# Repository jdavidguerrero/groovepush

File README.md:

# GroovePush

**DIY Ableton Push 3 clone + AI mix-copilot surface for the GroovePilot platform.**

A monorepo unifying the three layers of the controller:

| Layer | Path | Stack | Target |
|---|---|---|---|
| **Processor / firmware** | [`apps/processor`](apps/processor) | C++ / Arduino (PlatformIO) | Teensy 4.1 (brain) + NeoTrellis M4 (8×4 pads) |
| **GUI** | [`apps/gui`](apps/gui) | C++ / Qt 6 / QML | Raspberry Pi 5 + 5" DSI display |
| **Hardware** | [`hardware/`](hardware) | KiCad | Main PCB / interconnect |

Planning & contracts live in [`specs/`](specs) and [`docs/`](docs).

---

## Architecture at a glance

```
     ┌───────────────┐   USB-MIDI (class-compliant, <5ms)   ┌──────────┐
     │  Teensy 4.1   │─────────────────────────────────────▶│  Ableton │
     │  (Processor)  │                                       │   Live   │
     │  pads·enc·    │◀───── SysEx / Remote Script ──────────│          │
     │  faders·piezo │                                       └──────────┘
     └──────┬────────┘
            │ UART 1 Mbps (binary framing / SysEx)
            │  + I2C to 2× NeoTrellis (pads/LEDs)
     ┌──────┴────────┐   Serial (QSerialPort)   ┌───────────────────────┐
     │ NeoTrellis M4 │                          │  Raspberry Pi 5 (GUI) │
     │  8×4 pad grid │◀────── UART link ───────▶│  Qt/QML 5" display     │
     └───────────────┘                          │  + cloud AI (GroovePilot)
                                                 └───────────────────────┘
```

- **Performance MIDI never touches the network** — pads/encoders/faders reach Live as USB-MIDI from the Teensy.
- **The RPi5 GUI** is a thin, low-latency remote + the AI mix copilot surface.
- Wire protocol between Teensy ↔ M4 ↔ RPi is documented in [`specs/`](specs) and `apps/processor/include/shared/`.

## Repo layout

```
GroovePush/
├── apps/
│   ├── gui/          # Qt6/QML GUI (Raspberry Pi 5) — imported with full git history
│   └── processor/    # PlatformIO firmware (Teensy 4.1 + NeoTrellis M4) — full git history
├── hardware/         # KiCad project (schematic + PCB)
├── specs/            # OpenSpec-style specifications (source of truth for implementation)
├── docs/             # Design specs, guides, ADRs
├── .claude/          # Shared AI context, agents, and SDD harness
├── Makefile          # No-Node fallback orchestration
├── package.json      # pnpm workspace orchestration
└── pnpm-workspace.yaml
```

## Getting started

```bash
# With pnpm (workspace orchestration)
pnpm install
pnpm processor:build      # build firmware (PlatformIO)
pnpm gui:build            # build the Qt GUI

# Or with make (no Node required)
make help
make proc-build-teensy
make gui-build
```

### Prerequisites
- **Processor**: [PlatformIO Core](https://platformio.org/) (`pip install platformio`)
- **GUI**: Qt 6.8+, CMake ≥ 3.16 (see [`apps/gui/README_SETUP.md`](apps/gui/README_SETUP.md))
- **Hardware**: KiCad 8+

## History

`apps/gui` and `apps/processor` were previously two standalone GitHub repos
(`ableton_push_clone_gui`, `ableton_push_clone_processor`). They were merged into
this monorepo **preserving their full commit history** via `git subtree` merge.
The original remotes are preserved in `docs/MONOREPO_MIGRATION.md`.

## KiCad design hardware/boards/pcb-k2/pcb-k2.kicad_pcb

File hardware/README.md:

# GroovePush — Hardware (KiCad)

Modular hierarchical schematic for the GroovePush controller. See
[ADR-0001](../specs/adr/0001-modular-pcb-topology.md) for the topology decision.

- **Project**: `GroovePush.kicad_pro`
- **KiCad**: v10 (files `version 20260101`)
- **Root sheet**: `GroovePush.kicad_sch` → 4 sub-sheets (one per module / future PCB):
  `processor.kicad_sch`, `encoders.kicad_sch`, `analog.kicad_sch`, `leds.kicad_sch`.

## System topology

```
        ┌────────────────── PROCESSOR BOARD ──────────────────┐
        │  Teensy 4.1 (J1 socket)                              │
 +5V ──▶│  ├─ I2C ─ 2× MCP23017 (U1 0x20 sw, U2 0x21 btn)      │
 PSU  J4│  ├─ 4.7k I2C pull-ups (R1,R2)                        │
        │  └─ decoupling C1/C2/C3                              │
        │   J2      J3       J5/J8      J6        J7      J20   │
        └───┼───────┼─────────┼─────────┼─────────┼───────┼────┘
        I2C │  UART │  ribbon │ ribbon  │  3-wire │ ribbon│
        ┌───▼──┐ ┌──▼───┐ ┌───▼────┐ ┌──▼─────┐ ┌─▼────┐ │ panel
        │Neo-  │ │ RPi5 │ │ENCODER │ │ ANALOG │ │ LED  │ │ buttons
        │Trellis│ │ GUI │ │ board  │ │ board  │ │board │
        └──────┘ └──────┘ └────────┘ └────────┘ └──────┘
```

Each sub-sheet is electrically self-contained and exposes a header — it can become its
own PCB. The inter-board wiring is the **connector contract** in the table below.

## Bill of Materials (initial)

### Processor board (`processor.kicad_sch`)
| Ref | Value | Part | Notes |
|-----|-------|------|-------|
| J1 | Teensy 4.1 socket | 2×24 female header | The Teensy is a module; socket pinout must be mapped to the real Teensy 4.1 footprint before layout |
| U1 | MCP23017 @ 0x20 | I²C 16-bit I/O expander | 8 encoder push-switches (GPA0–6 + GPB0) |
| U2 | MCP23017 @ 0x21 | I²C 16-bit I/O expander | 8 extra panel buttons (GPA0–6 + GPB0) |
| R1, R2 | 4.7 kΩ | I²C pull-ups | SDA / SCL to +3V3 |
| C1, C2 | 100 nF | Decoupling | 1 per MCP23017 |
| C3 | 10 µF | Bulk | +5V rail |
| J2 | 1×4 | NeoTrellis I²C | SDA, SCL, +3V3, GND |
| J3 | 1×4 | RPi5 UART | TX, RX, GND, GND |
| J4 | 1×2 | 5 V power in | +5V, GND |
| J5 | 2×8 | Encoder A/B ribbon | 16 quadrature lines |
| J6 | 1×12 | Analog board | 4 fader + 4 piezo + 2 IR + 3V3 + GND |
| J7 | 1×3 | LED board | LED_DATA, +5V, GND |
| J8 | 1×10 | Encoder switches | 8 switches + GND |
| J20 | 1×10 | Panel buttons | 8 buttons + 2 GND |

### Encoder board (`encoders.kicad_sch`)
| Ref | Value | Part | Notes |
|-----|-------|------|-------|
| RE1–RE8 | EC11 | Rotary encoder + switch | A/B quadrature + push |
| J9 | 2×8 | A/B to processor | mates J5 |
| J10 | 1×10 | Switches to processor | mates J8 |

### Analog board (`analog.kicad_sch`)
| Ref | Value | Part | Notes |
|-----|-------|------|-------|
| RV1–RV4 | ALPS B50K | Slide potentiometer (fader) | wiper → ADC |
| J12–J15 | 1×2 | Piezo element | signal + GND |
| R3–R6 | 1 MΩ | Piezo bleed | across each piezo |
| J16, J17 | 1×3 | Sharp IR sensor | +3V3, GND, OUT |
| J11 | 1×12 | To processor | mates J6 |

### LED board (`leds.kicad_sch`)
| Ref | Value | Part | Notes |
|-----|-------|------|-------|
| U3 | SN74LVC245A | Level shifter 3.3→5 V | data line to strip |
| R7 | 330 Ω | Series | data protection |
| D1 | WS2812B | First pixel (strip = 28) | DIN←data, DOUT→strip |
| C4 | 1000 µF | Bulk | +5V near LEDs |
| C5 | 100 nF | Decoupling | U3 |
| J18 | 1×3 | To LED strip | +5V, DATA, GND |
| J19 | 1×3 | To processor | mates J7 |

## Inter-board connector contract

| Processor conn | Mates | Signals | Cable |
|---|---|---|---|
| J2 | NeoTrellis board | I2C_SDA, I2C_SCL, +3V3, GND | 4-wire |
| J3 | Raspberry Pi 5 | TEENSY_TX1→RPi_RX, TEENSY_RX1→RPi_TX, GND, GND | 4-wire (do **not** power the Pi from here) |
| J4 | 5 V PSU | +5V, GND | 5 V / 3 A min |
| J5 ↔ J9 | Encoder board | ENC1..8 A/B (16) | 16-way ribbon |
| J8 ↔ J10 | Encoder board | ENC_SW1..8, GND | 10-way ribbon |
| J6 ↔ J11 | Analog board | FADER1..4, PIEZO1..4, IR1..2, +3V3, GND | 12-way |
| J7 ↔ J19 | LED board | LED_DATA, +5V, GND | 3-wire |
| J20 | Panel buttons | BTN1..8, GND | 10-way |

## Power budget (from `apps/processor/PIN_DISTRIBUTION.md`)
| Rail | Load | Current |
|---|---|---|
| +5V | NeoPixels (28 @ full) | ~1.7 A |
| +5V | Teensy 4.1 | ~0.15 A |
| +3V3 | 2× NeoTrellis, MCP, encoders, sensors | ~0.25 A |
| **Total** | | **5 V / 3 A PSU minimum** |

## Verification status
Connectivity validated via the KiCad MCP net lister (all nets ≥ 2 pins; power rails carry
`PWR_FLAG`; unused MCP/level-shifter pins marked no-connect). Full ERC/netlist export via
`kicad-cli` was **not run in this environment** (no `kicad-cli` on PATH). Open the project
in KiCad 10 and run ERC before layout.

## Known issues / next steps (see `../GAPS_AND_IMPROVEMENTS.md`)
1. **Footprints not yet assigned** — this is schematic-only. Assign before PCB layout.
2. **Teensy socket pin mapping** — J1 pins are logical; map to the real Teensy 4.1
   footprint (verify each GPIO ↔ socket position) before layout.
3. **I2C vs UART NeoTrellis** — this design uses I²C NeoTrellis (0x2E/0x2F) per the user's
   build; the firmware's `UART_CONNECTIONS.md` (NeoTrellis **M4** over UART) is an
   alternative. Reconcile firmware `Config.h` accordingly.
4. **Sharp IR level** — powered from +3V3; select a 3.3 V-compatible rangefinder, or add a
   divider if using a 5 V GP2Y0A part (its output can exceed 3.3 V).
5. **MCP23017 GPA7/GPB7** are output-only (erratum) — intentionally not used as inputs.
6. **Encoder A/B pull-ups** — rely on Teensy internal pull-ups; add external 10 k if noisy.

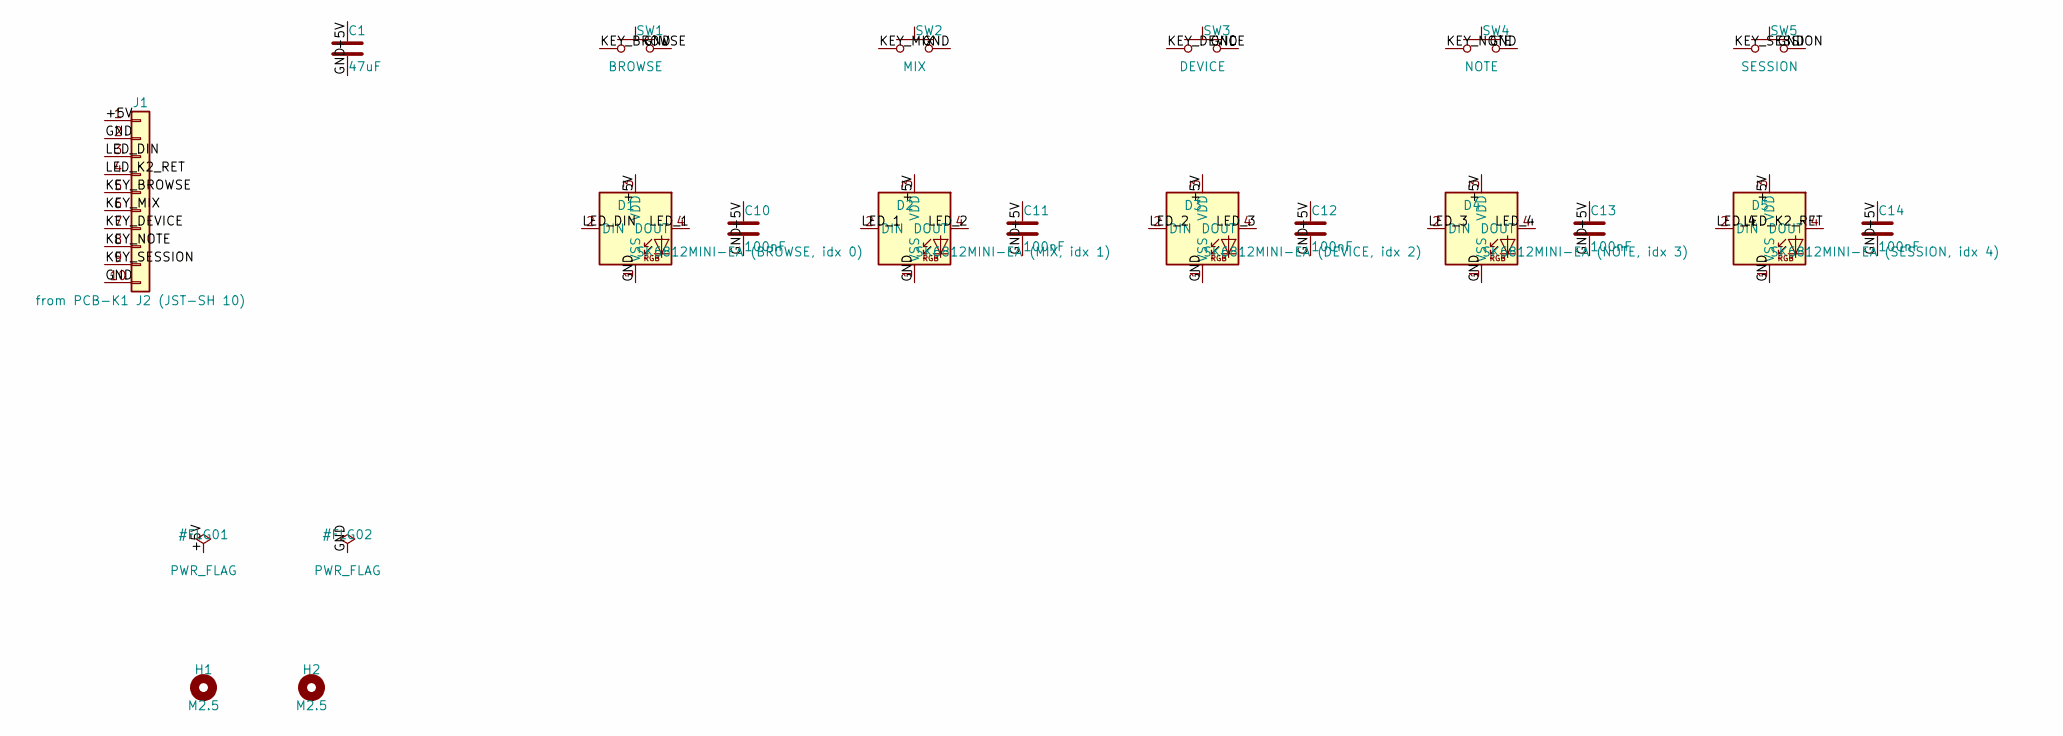
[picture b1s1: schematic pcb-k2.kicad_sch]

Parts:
C1: 47uF; C_1206_3216Metric
C10, C11, C12, C13, C14: 100nF; C_0603_1608Metric
D1: SK6812MINI-EA (BROWSE, idx 0); LED_SK6812MINI-E_3.2x2.8mm_P1.5mm_ReverseMount
D2: SK6812MINI-EA (MIX, idx 1); LED_SK6812MINI-E_3.2x2.8mm_P1.5mm_ReverseMount
D3: SK6812MINI-EA (DEVICE, idx 2); LED_SK6812MINI-E_3.2x2.8mm_P1.5mm_ReverseMount
D4: SK6812MINI-EA (NOTE, idx 3); LED_SK6812MINI-E_3.2x2.8mm_P1.5mm_ReverseMount
D5: SK6812MINI-EA (SESSION, idx 4); LED_SK6812MINI-E_3.2x2.8mm_P1.5mm_ReverseMount
H1, H2: M2.5; MountingHole_2.7mm_M2.5
J1: from PCB-K1 J2 (JST-SH 10); JST_SH_SM10B-SRSS-TB_1x10-1MP_P1.00mm_Horizontal
SW1: BROWSE; SW_Kailh_Choc_V2_1u
SW2: MIX; SW_Kailh_Choc_V2_1u
SW3: DEVICE; SW_Kailh_Choc_V2_1u
SW4: NOTE; SW_Kailh_Choc_V2_1u
SW5: SESSION; SW_Kailh_Choc_V2_1u

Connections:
/+5V: C1.1, C10.1, C11.1, C12.1, C13.1, C14.1, D1.3 (VDD), D2.3 (VDD), D3.3 (VDD), D4.3 (VDD), D5.3 (VDD), J1.1
/GND: C1.2, C10.2, C11.2, C12.2, C13.2, C14.2, D1.1 (VSS), D2.1 (VSS), D3.1 (VSS), D4.1 (VSS), D5.1 (VSS), J1.2, J1.10, SW1.2, SW2.2, SW3.2, SW4.2, SW5.2
/KEY_BROWSE: J1.5, SW1.1
/KEY_DEVICE: J1.7, SW3.1
/KEY_MIX: J1.6, SW2.1
/KEY_NOTE: J1.8, SW4.1
/KEY_SESSION: J1.9, SW5.1
/LED_1: D1.4 (DOUT), D2.2 (DIN)
/LED_2: D2.4 (DOUT), D3.2 (DIN)
/LED_3: D3.4 (DOUT), D4.2 (DIN)
/LED_4: D4.4 (DOUT), D5.2 (DIN)
/LED_DIN: D1.2 (DIN), J1.3
/LED_K2_RET: D5.4 (DOUT), J1.4

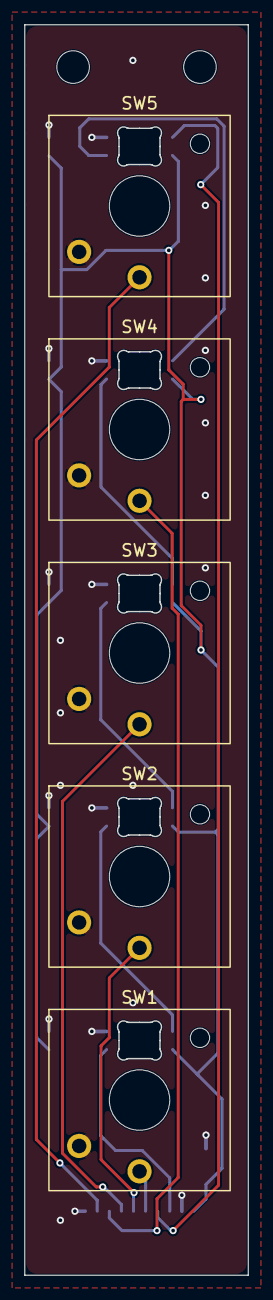
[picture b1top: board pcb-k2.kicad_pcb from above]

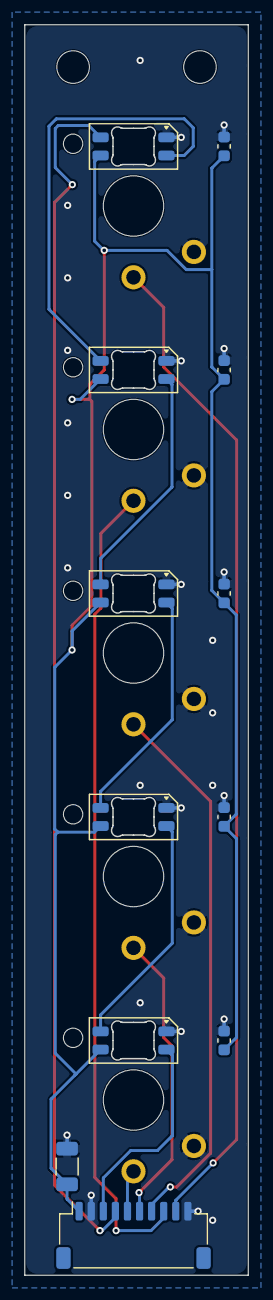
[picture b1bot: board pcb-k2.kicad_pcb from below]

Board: 2 copper layers, 18.5 x 103.5 mm, 19 parts (12 on the bottom side), 13 nets.

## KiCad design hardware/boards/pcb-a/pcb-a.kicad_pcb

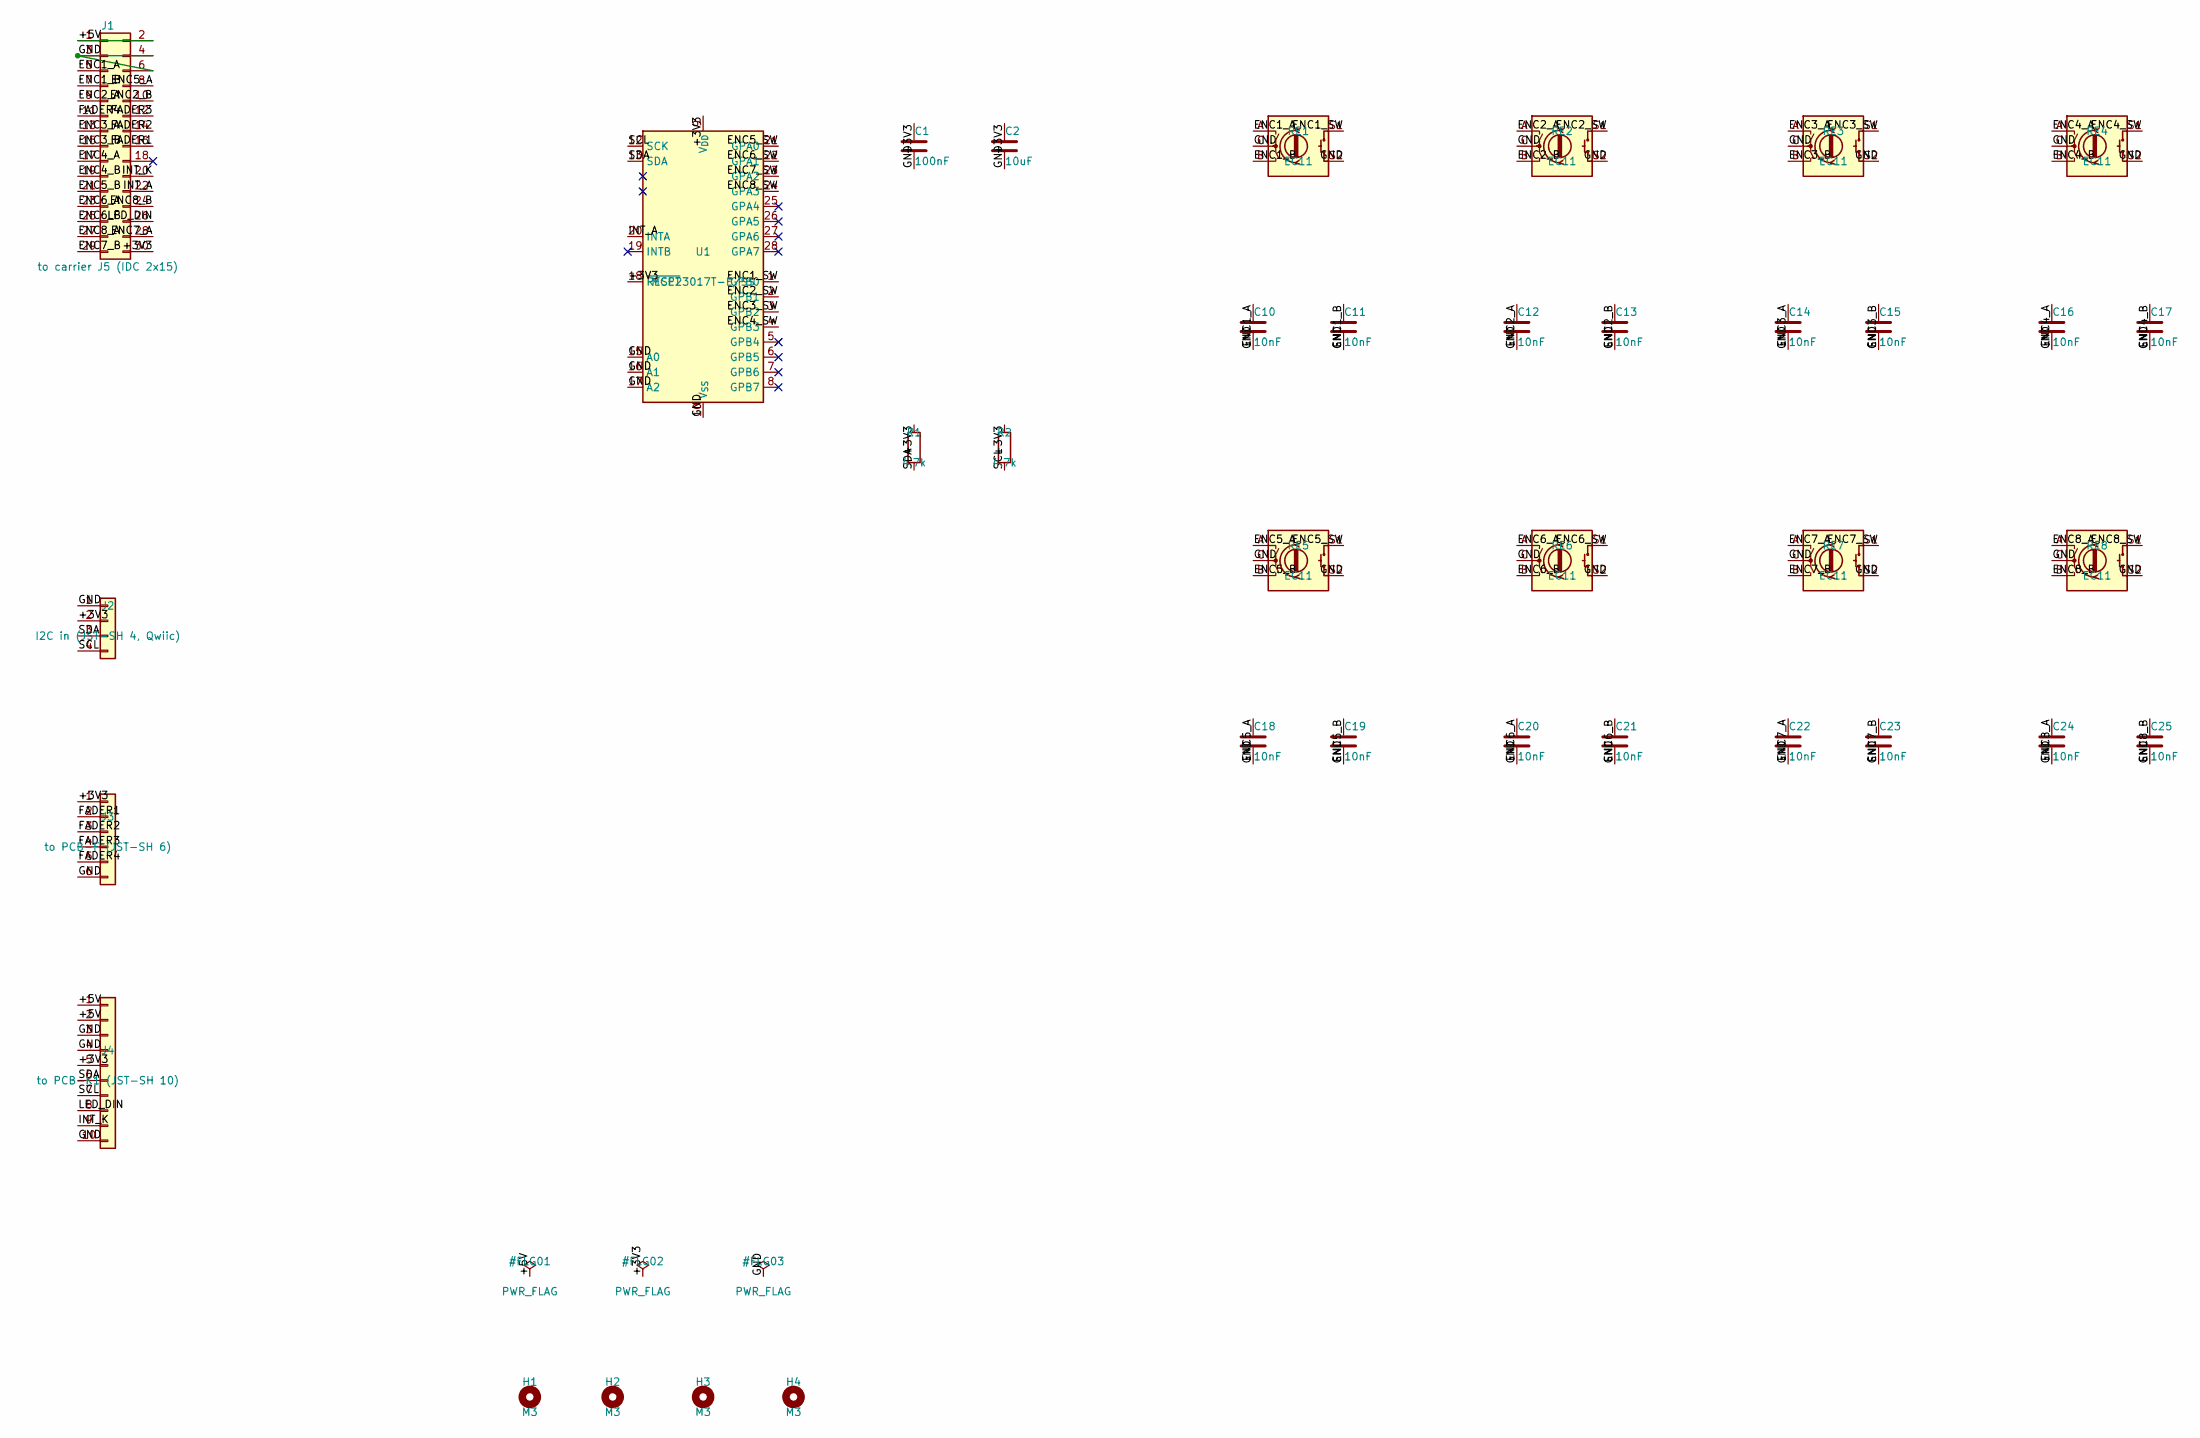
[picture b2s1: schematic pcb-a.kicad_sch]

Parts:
C1: 100nF; C_0603_1608Metric; LCSC C14663
C2: 10uF; C_0805_2012Metric; LCSC C15850
C10, C11, C12, C13, C14, C15, C16, C17, C18, C19, C20, C21, C22, C23, C24, C25: 10nF; C_0603_1608Metric; LCSC C57112
H1, H2, H3, H4: M3; MountingHole_3.2mm_M3
J1: to carrier J5 (IDC 2x15); IDC-Header_2x15_P2.54mm_Vertical
J2: I2C in (JST-SH 4, Qwiic); JST_SH_SM04B-SRSS-TB_1x04-1MP_P1.00mm_Horizontal; LCSC C160404
J3: to PCB-F (JST-SH 6); JST_SH_SM06B-SRSS-TB_1x06-1MP_P1.00mm_Horizontal; LCSC C160405
J4: to PCB-K1 (JST-SH 10); JST_SH_SM10B-SRSS-TB_1x10-1MP_P1.00mm_Horizontal; LCSC C160409
R1, R2: 4.7k; R_0603_1608Metric; LCSC C23162
RE1, RE2, RE3, RE4, RE5, RE6, RE7, RE8: EC11; RotaryEncoder_Alps_EC11E-Switch_Vertical_H20mm
U1: MCP23017T-E/SS; SSOP-28_5.3x10.2mm_P0.65mm; LCSC C558584

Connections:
/+3V3: C1.1, C2.1, J1.30, J2.2, J3.1, J4.5, R1.1, R2.1, U1.9 (V_{DD}), U1.18 (~RESET)
/+5V: J1.1, J1.2, J4.1, J4.2
/ENC1_A: C10.1, J1.5, RE1.A
/ENC1_B: C11.1, J1.7, RE1.B
/ENC1_SW: RE1.S1, U1.1 (GPB0)
/ENC2_A: C12.1, J1.9, RE2.A
/ENC2_B: C13.1, J1.10, RE2.B
/ENC2_SW: RE2.S1, U1.2 (GPB1)
/ENC3_A: C14.1, J1.13, RE3.A
/ENC3_B: C15.1, J1.15, RE3.B
/ENC3_SW: RE3.S1, U1.3 (GPB2)
/ENC4_A: C16.1, J1.17, RE4.A
/ENC4_B: C17.1, J1.19, RE4.B
/ENC4_SW: RE4.S1, U1.4 (GPB3)
/ENC5_A: C18.1, J1.8, RE5.A
/ENC5_B: C19.1, J1.21, RE5.B
/ENC5_SW: RE5.S1, U1.21 (GPA0)
/ENC6_A: C20.1, J1.23, RE6.A
/ENC6_B: C21.1, J1.25, RE6.B
/ENC6_SW: RE6.S1, U1.22 (GPA1)
/ENC7_A: C22.1, J1.28, RE7.A
/ENC7_B: C23.1, J1.29, RE7.B
/ENC7_SW: RE7.S1, U1.23 (GPA2)
/ENC8_A: C24.1, J1.27, RE8.A
/ENC8_B: C25.1, J1.24, RE8.B
/ENC8_SW: RE8.S1, U1.24 (GPA3)
/FADER1: J1.16, J3.2
/FADER2: J1.14, J3.3
/FADER3: J1.12, J3.4
/FADER4: J1.11, J3.5
/GND: C1.2, C2.2, C10.2, C11.2, C12.2, C13.2, C14.2, C15.2, C16.2, C17.2, C18.2, C19.2, C20.2, C21.2, C22.2, C23.2, C24.2, C25.2, J1.3, J1.4, J1.6, J2.1, J3.6, J4.3, J4.4, J4.10, RE1.C, RE1.S2, RE2.C, RE2.S2, RE3.C, RE3.S2, RE4.C, RE4.S2, RE5.C, RE5.S2, RE6.C, RE6.S2, RE7.C, RE7.S2, RE8.C, RE8.S2, U1.10 (V_{SS}), U1.15 (A0), U1.16 (A1), U1.17 (A2)
/INT_A: J1.22, U1.20 (INTA)
/INT_K: J1.20, J4.9
/LED_DIN: J1.26, J4.8
/SCL: J2.4, J4.7, R2.2, U1.12 (SCK)
/SDA: J2.3, J4.6, R1.2, U1.13 (SDA)

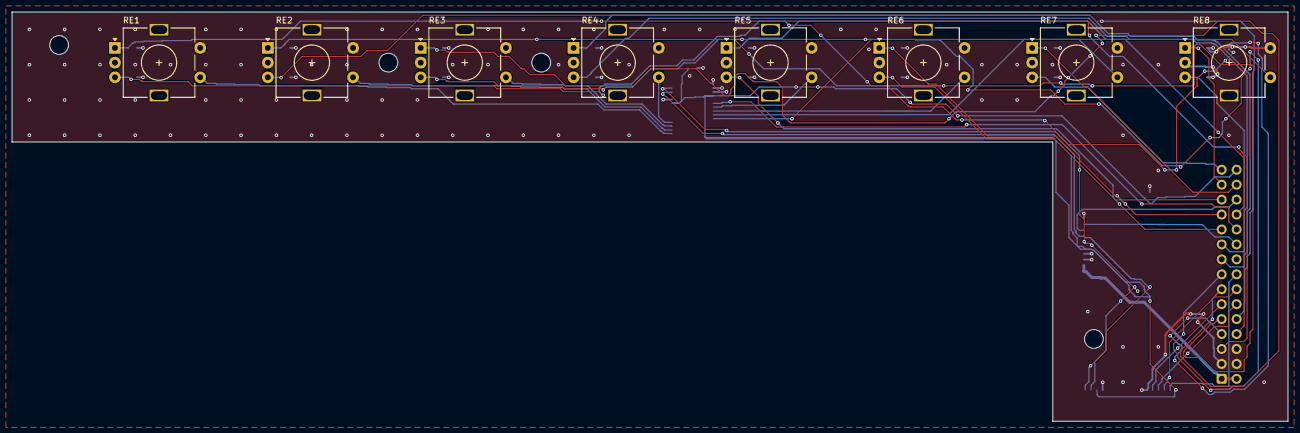
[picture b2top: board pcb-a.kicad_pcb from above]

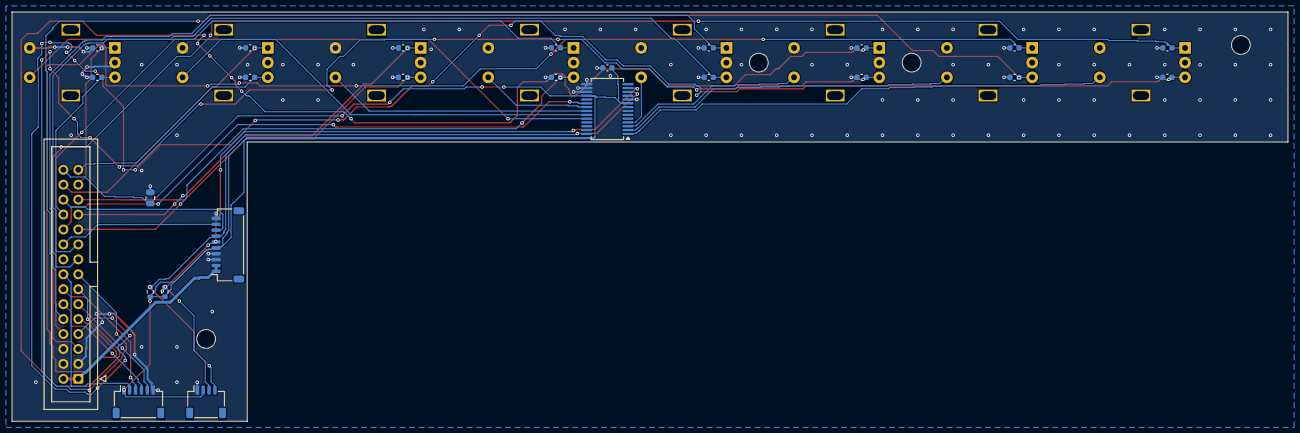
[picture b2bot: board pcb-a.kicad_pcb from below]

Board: 2 copper layers, 217.0 x 69.6 mm, 37 parts (25 on the bottom side), 36 nets.

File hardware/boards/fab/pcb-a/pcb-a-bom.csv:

Comment,Designator,Footprint,LCSC Part #
100nF,C1,C_0603_1608Metric,C14663
10uF,C2,C_0805_2012Metric,C15850
10nF,"C10,C11,C12,C13,C14,C15,C16,C17,C18,C19,C20,C21,C22,C23,C24,C25",C_0603_1608Metric,C57112
SM04B-SRSS-TB,J2,JST_SH_SM04B-SRSS-TB_1x04-1MP_P1.00mm_Horizontal,C160404
SM06B-SRSS-TB,J3,JST_SH_SM06B-SRSS-TB_1x06-1MP_P1.00mm_Horizontal,C160405
SM10B-SRSS-TB,J4,JST_SH_SM10B-SRSS-TB_1x10-1MP_P1.00mm_Horizontal,C160409
4.7k,"R1,R2",R_0603_1608Metric,C23162
MCP23017T-E/SS,U1,SSOP-28_5.3x10.2mm_P0.65mm,C558584

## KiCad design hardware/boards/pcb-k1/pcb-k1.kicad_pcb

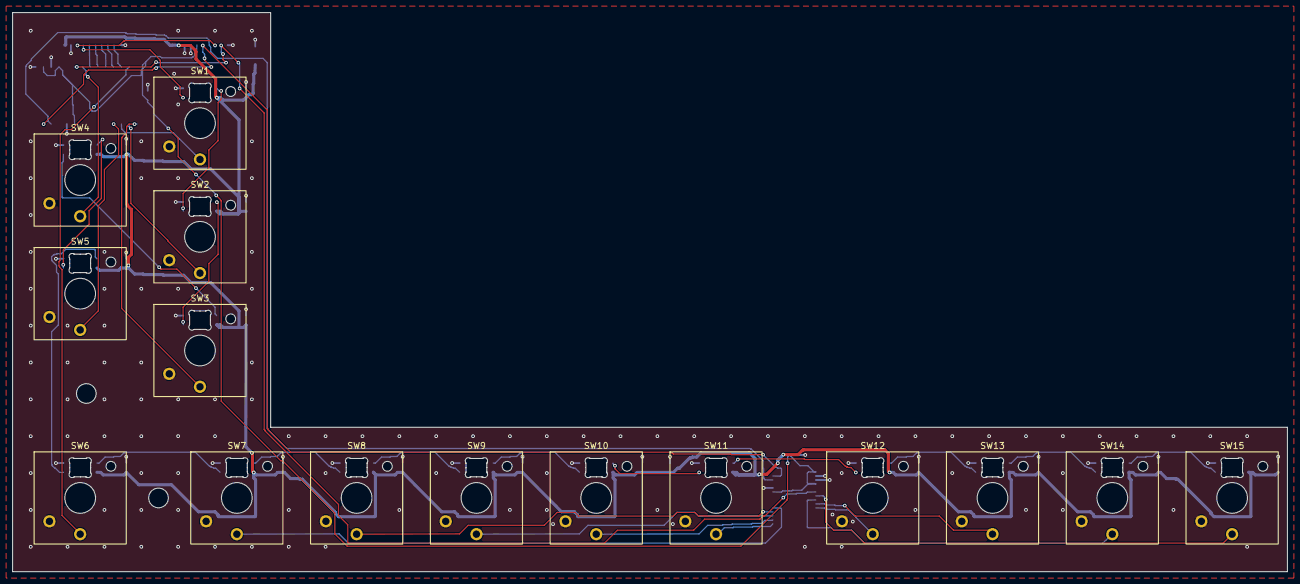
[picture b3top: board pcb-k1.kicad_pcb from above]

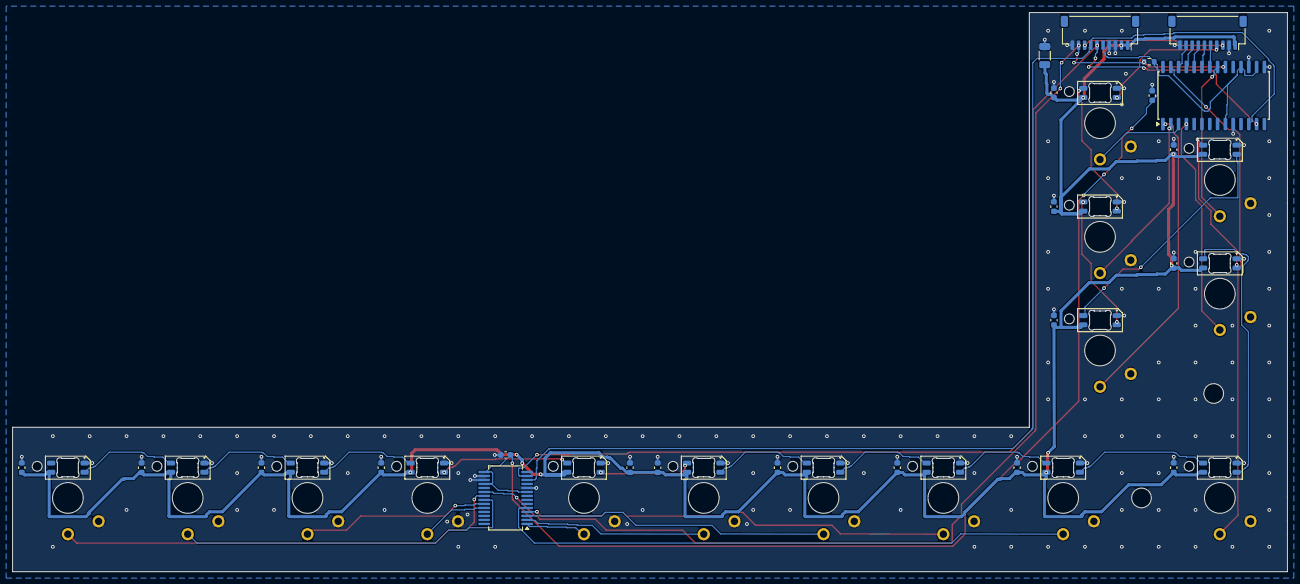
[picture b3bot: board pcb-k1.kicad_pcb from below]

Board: 2 copper layers, 207.5 x 91.0 mm, 55 parts (38 on the bottom side), 42 nets.

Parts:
C1, C2, C10, C11, C12, C13, C14, C15, C16, C17, C18, C19, C20, C21, C22, C23, C24: 100nF; C_0603_1608Metric
C3: 47uF; C_1206_3216Metric
D1: SK6812MINI-EA (QUANTIZE, idx 5); LED_SK6812MINI-E_3.2x2.8mm_P1.5mm_ReverseMount
D2: SK6812MINI-EA (DUPLICATE, idx 6); LED_SK6812MINI-E_3.2x2.8mm_P1.5mm_ReverseMount
D3: SK6812MINI-EA (DELETE, idx 7); LED_SK6812MINI-E_3.2x2.8mm_P1.5mm_ReverseMount
D4: SK6812MINI-EA (UNDO, idx 8); LED_SK6812MINI-E_3.2x2.8mm_P1.5mm_ReverseMount
D5: SK6812MINI-EA (NEW, idx 9); LED_SK6812MINI-E_3.2x2.8mm_P1.5mm_ReverseMount
D6: SK6812MINI-EA (SHIFT, idx 10); LED_SK6812MINI-E_3.2x2.8mm_P1.5mm_ReverseMount
D7: SK6812MINI-EA (PLAY, idx 11); LED_SK6812MINI-E_3.2x2.8mm_P1.5mm_ReverseMount
D8: SK6812MINI-EA (STOP, idx 12); LED_SK6812MINI-E_3.2x2.8mm_P1.5mm_ReverseMount
D9: SK6812MINI-EA (RECORD, idx 13); LED_SK6812MINI-E_3.2x2.8mm_P1.5mm_ReverseMount
D10: SK6812MINI-EA (LOOP, idx 14); LED_SK6812MINI-E_3.2x2.8mm_P1.5mm_ReverseMount
D11: SK6812MINI-EA (METRO, idx 15); LED_SK6812MINI-E_3.2x2.8mm_P1.5mm_ReverseMount
D12: SK6812MINI-EA (BANK_L, idx 16); LED_SK6812MINI-E_3.2x2.8mm_P1.5mm_ReverseMount
D13: SK6812MINI-EA (BANK_R, idx 17); LED_SK6812MINI-E_3.2x2.8mm_P1.5mm_ReverseMount
D14: SK6812MINI-EA (OCT_DN, idx 18); LED_SK6812MINI-E_3.2x2.8mm_P1.5mm_ReverseMount
D15: SK6812MINI-EA (OCT_UP, idx 19); LED_SK6812MINI-E_3.2x2.8mm_P1.5mm_ReverseMount
H1, H2: M3; MountingHole_3.2mm_M3
J1: from PCB-A J4 (JST-SH 10); JST_SH_SM10B-SRSS-TB_1x10-1MP_P1.00mm_Horizontal
J2: to PCB-K2 J1 (JST-SH 10); JST_SH_SM10B-SRSS-TB_1x10-1MP_P1.00mm_Horizontal
R1: 10k; R_0603_1608Metric
SW1: QUANTIZE; SW_Kailh_Choc_V2_1u
SW2: DUPLICATE; SW_Kailh_Choc_V2_1u
SW3: DELETE; SW_Kailh_Choc_V2_1u
SW4: UNDO; SW_Kailh_Choc_V2_1u
SW5: NEW; SW_Kailh_Choc_V2_1u
SW6: SHIFT; SW_Kailh_Choc_V2_1u
SW7: PLAY; SW_Kailh_Choc_V2_1u
SW8: STOP; SW_Kailh_Choc_V2_1u
SW9: RECORD; SW_Kailh_Choc_V2_1u
SW10: LOOP; SW_Kailh_Choc_V2_1u
SW11: METRO; SW_Kailh_Choc_V2_1u
SW12: BANK_L; SW_Kailh_Choc_V2_1u
SW13: BANK_R; SW_Kailh_Choc_V2_1u
SW14: OCT_DN; SW_Kailh_Choc_V2_1u
SW15: OCT_UP; SW_Kailh_Choc_V2_1u
U1: MCP23017T-E/SS @0x21; SSOP-28_5.3x10.2mm_P0.65mm
U2: MCP23017-E/SO @0x22; SOIC-28W_7.5x17.9mm_P1.27mm

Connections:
/+3V3: C1.1, C2.1, J1.5, R1.1, U1.9, U1.15, U1.18, U2.9, U2.16, U2.18
/+5V: C3.1, C10.1, C11.1, C12.1, C13.1, C14.1, C15.1, C16.1, C17.1, C18.1, C19.1, C20.1, C21.1, C22.1, C23.1, C24.1, D1.3, D2.3, D3.3, D4.3, D5.3, D6.3, D7.3, D8.3, D9.3, D10.3, D11.3, D12.3, D13.3, D14.3, D15.3, J1.1, J1.2, J2.1
/GND: C1.2, C2.2, C3.2, C10.2, C11.2, C12.2, C13.2, C14.2, C15.2, C16.2, C17.2, C18.2, C19.2, C20.2, C21.2, C22.2, C23.2, C24.2, D1.1, D2.1, D3.1, D4.1, D5.1, D6.1, D7.1, D8.1, D9.1, D10.1, D11.1, D12.1, D13.1, D14.1, D15.1, J1.3, J1.4, J1.10, J2.2, J2.10, SW1.2, SW2.2, SW3.2, SW4.2, SW5.2, SW6.2, SW7.2, SW8.2, SW9.2, SW10.2, SW11.2, SW12.2, SW13.2, SW14.2, SW15.2, U1.10, U1.16, U1.17, U2.10, U2.15, U2.17
/INT_K: J1.9, R1.2, U1.20, U2.20
/KEY_BANK_L: SW12.1, U1.24
/KEY_BANK_R: SW13.1, U1.23
/KEY_BROWSE: J2.5, U2.22
/KEY_DELETE: SW3.1, U2.1
/KEY_DEVICE: J2.7, U2.24
/KEY_DUPLICATE: SW2.1, U2.2
/KEY_LOOP: SW10.1, U1.2
/KEY_METRO: SW11.1, U1.1
/KEY_MIX: J2.6, U2.23
/KEY_NEW: SW5.1, U2.4
/KEY_NOTE: J2.8, U2.25
/KEY_OCT_DN: SW14.1, U1.22
/KEY_OCT_UP: SW15.1, U1.21
/KEY_PLAY: SW7.1, U1.5
/KEY_QUANTIZE: SW1.1, U2.3
/KEY_RECORD: SW9.1, U1.3
/KEY_SESSION: J2.9, U2.26
/KEY_SHIFT: SW6.1, U2.27
/KEY_STOP: SW8.1, U1.4
/KEY_UNDO: SW4.1, U2.21
/LED_1: D1.4, D2.2
/LED_2: D2.4, D3.2
/LED_3: D3.4, D4.2
/LED_4: D4.4, D5.2
/LED_5: D5.4, D6.2
/LED_6: D6.4, D7.2
/LED_7: D7.4, D8.2
/LED_8: D8.4, D9.2
/LED_9: D9.4, D10.2
/LED_10: D10.4, D11.2
/LED_11: D11.4, D12.2
/LED_12: D12.4, D13.2
/LED_13: D13.4, D14.2
/LED_14: D14.4, D15.2
/LED_DIN: J1.8, J2.3
/LED_K2_RET: D1.2, J2.4
/SCL: J1.7, U1.12, U2.12
/SDA: J1.6, U1.13, U2.13

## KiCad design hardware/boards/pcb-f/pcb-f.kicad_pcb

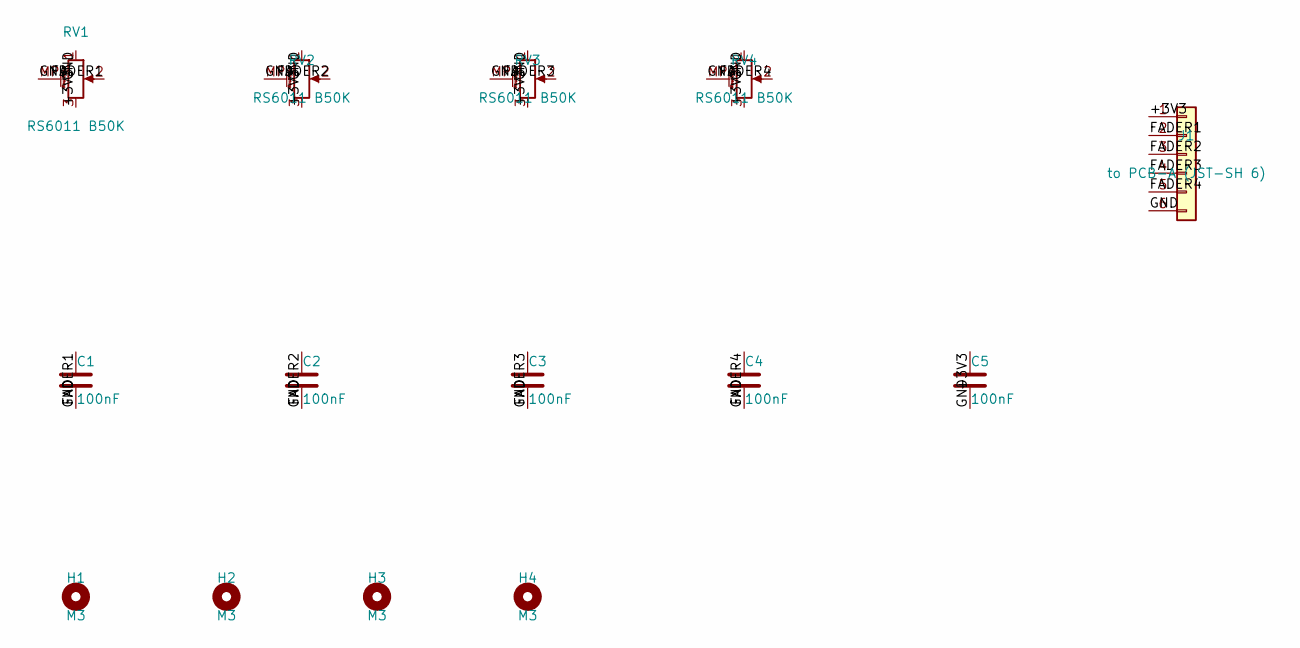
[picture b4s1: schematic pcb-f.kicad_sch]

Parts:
C1, C2, C3, C4, C5: 100nF; C_0603_1608Metric
H1, H2, H3, H4: M3; MountingHole_3.2mm_M3
J1: to PCB-A (JST-SH 6); JST_SH_SM06B-SRSS-TB_1x06-1MP_P1.00mm_Horizontal
RV1, RV2, RV3, RV4: RS6011 B50K; ALPS_RS6011P_60mm

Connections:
/+3V3: C5.1, J1.1, RV1.3, RV2.3, RV3.3, RV4.3
/FADER1: C1.1, J1.2, RV1.2
/FADER2: C2.1, J1.3, RV2.2
/FADER3: C3.1, J1.4, RV3.2
/FADER4: C4.1, J1.5, RV4.2
/GND: C1.2, C2.2, C3.2, C4.2, C5.2, J1.6, RV1.1, RV1.MP (MountPin), RV2.1, RV2.MP (MountPin), RV3.1, RV3.MP (MountPin), RV4.1, RV4.MP (MountPin)

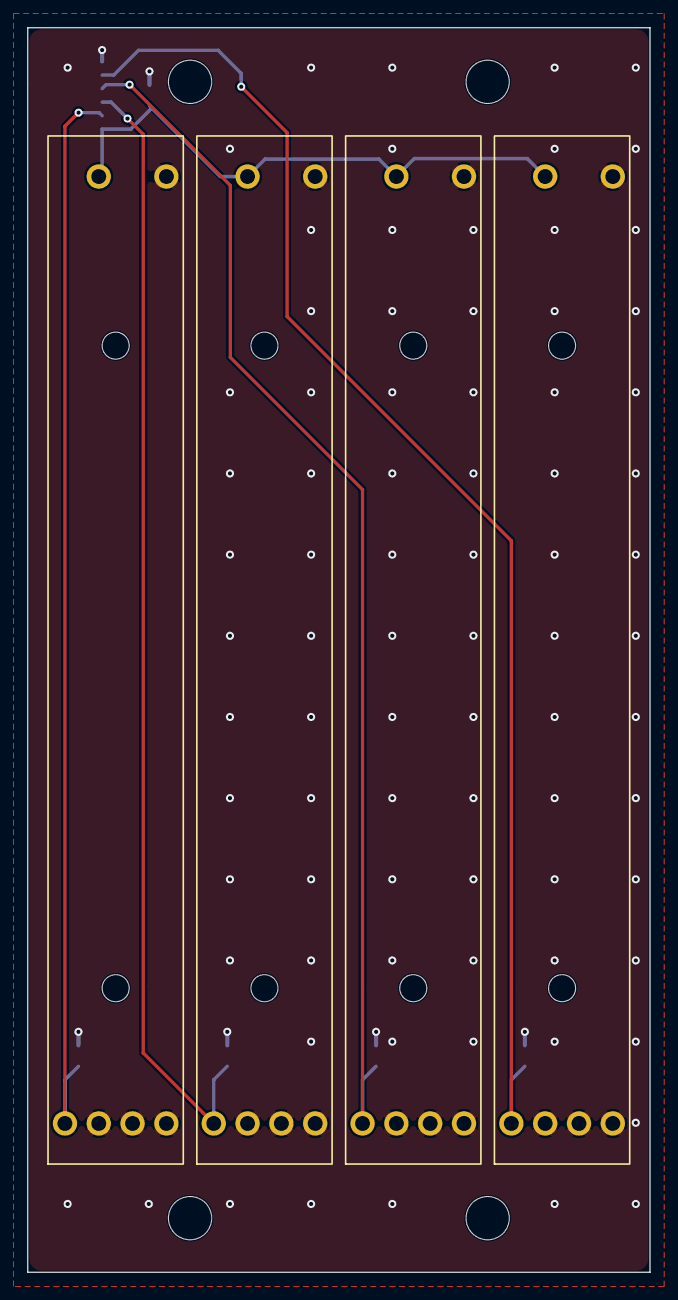
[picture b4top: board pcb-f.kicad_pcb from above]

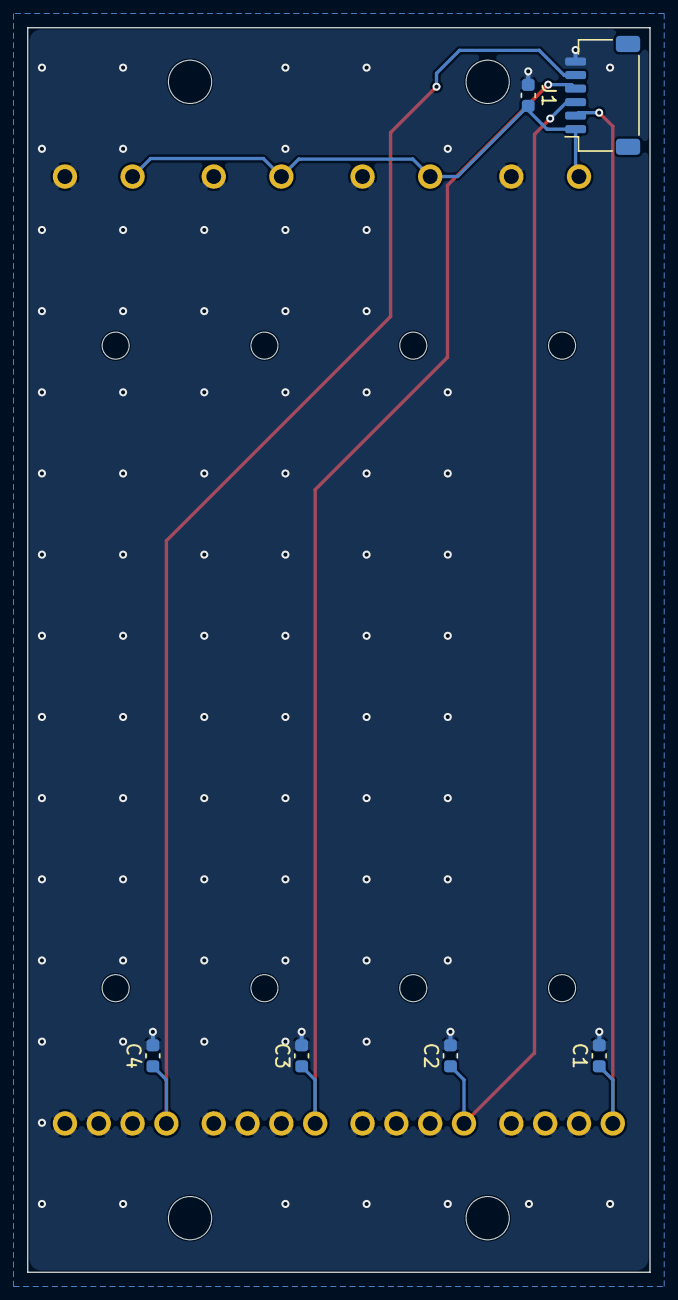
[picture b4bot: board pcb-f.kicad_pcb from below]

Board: 2 copper layers, 46.0 x 92.0 mm, 14 parts (6 on the bottom side), 6 nets.
